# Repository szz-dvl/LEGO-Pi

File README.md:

LEGO-Pi
=======

This is my final degree project. Its is a HAL to control LEGO peripherals from a Raspberry Pi, for more detailed info please refer to the [docs](https://github.com/szz-dvl/LEGO-Pi/tree/master/docs) directory.

## Acknowledgments

* F.I.B: Facultad d'Informàtica de Barcelona.

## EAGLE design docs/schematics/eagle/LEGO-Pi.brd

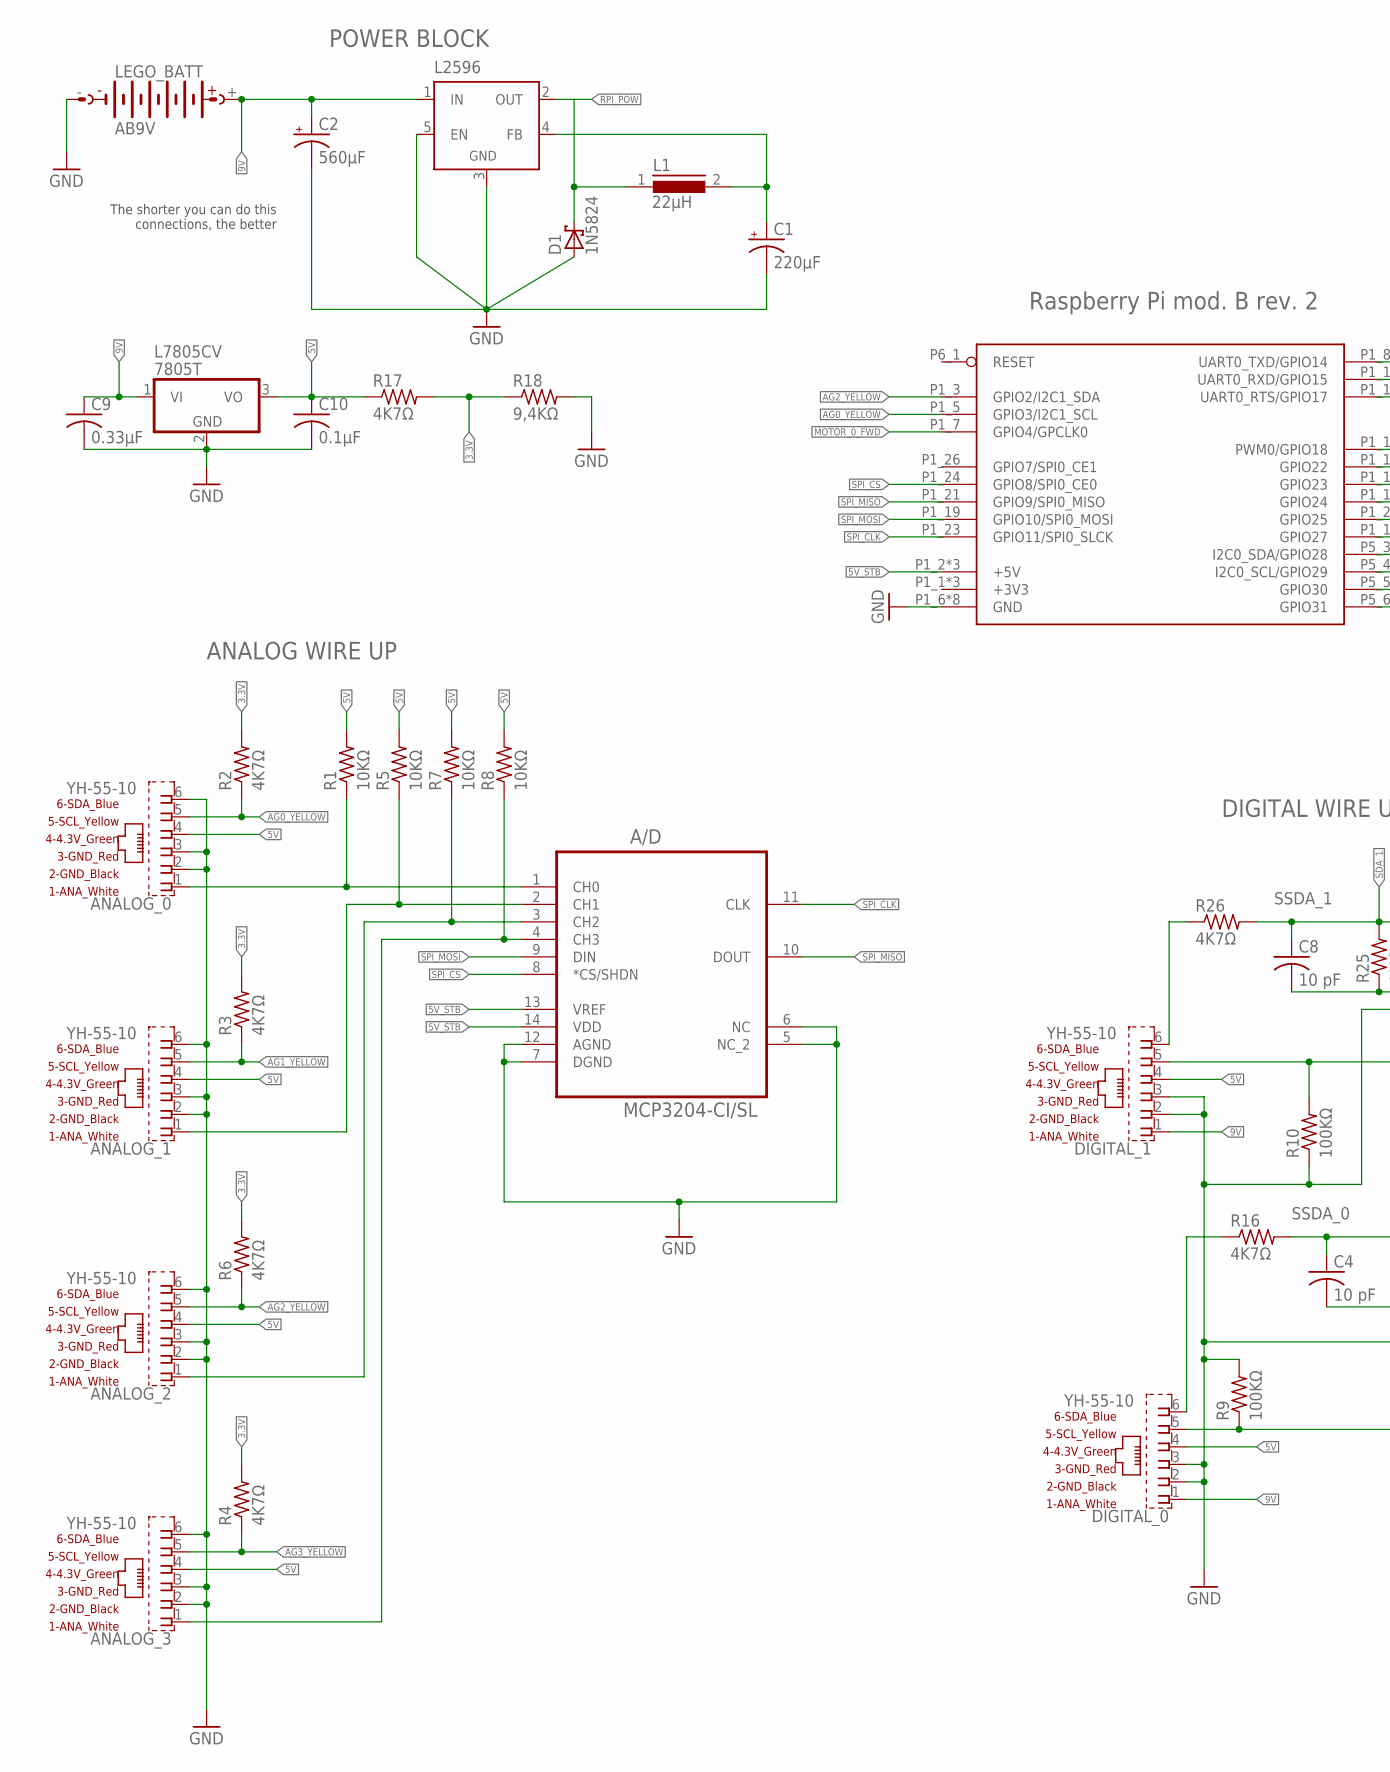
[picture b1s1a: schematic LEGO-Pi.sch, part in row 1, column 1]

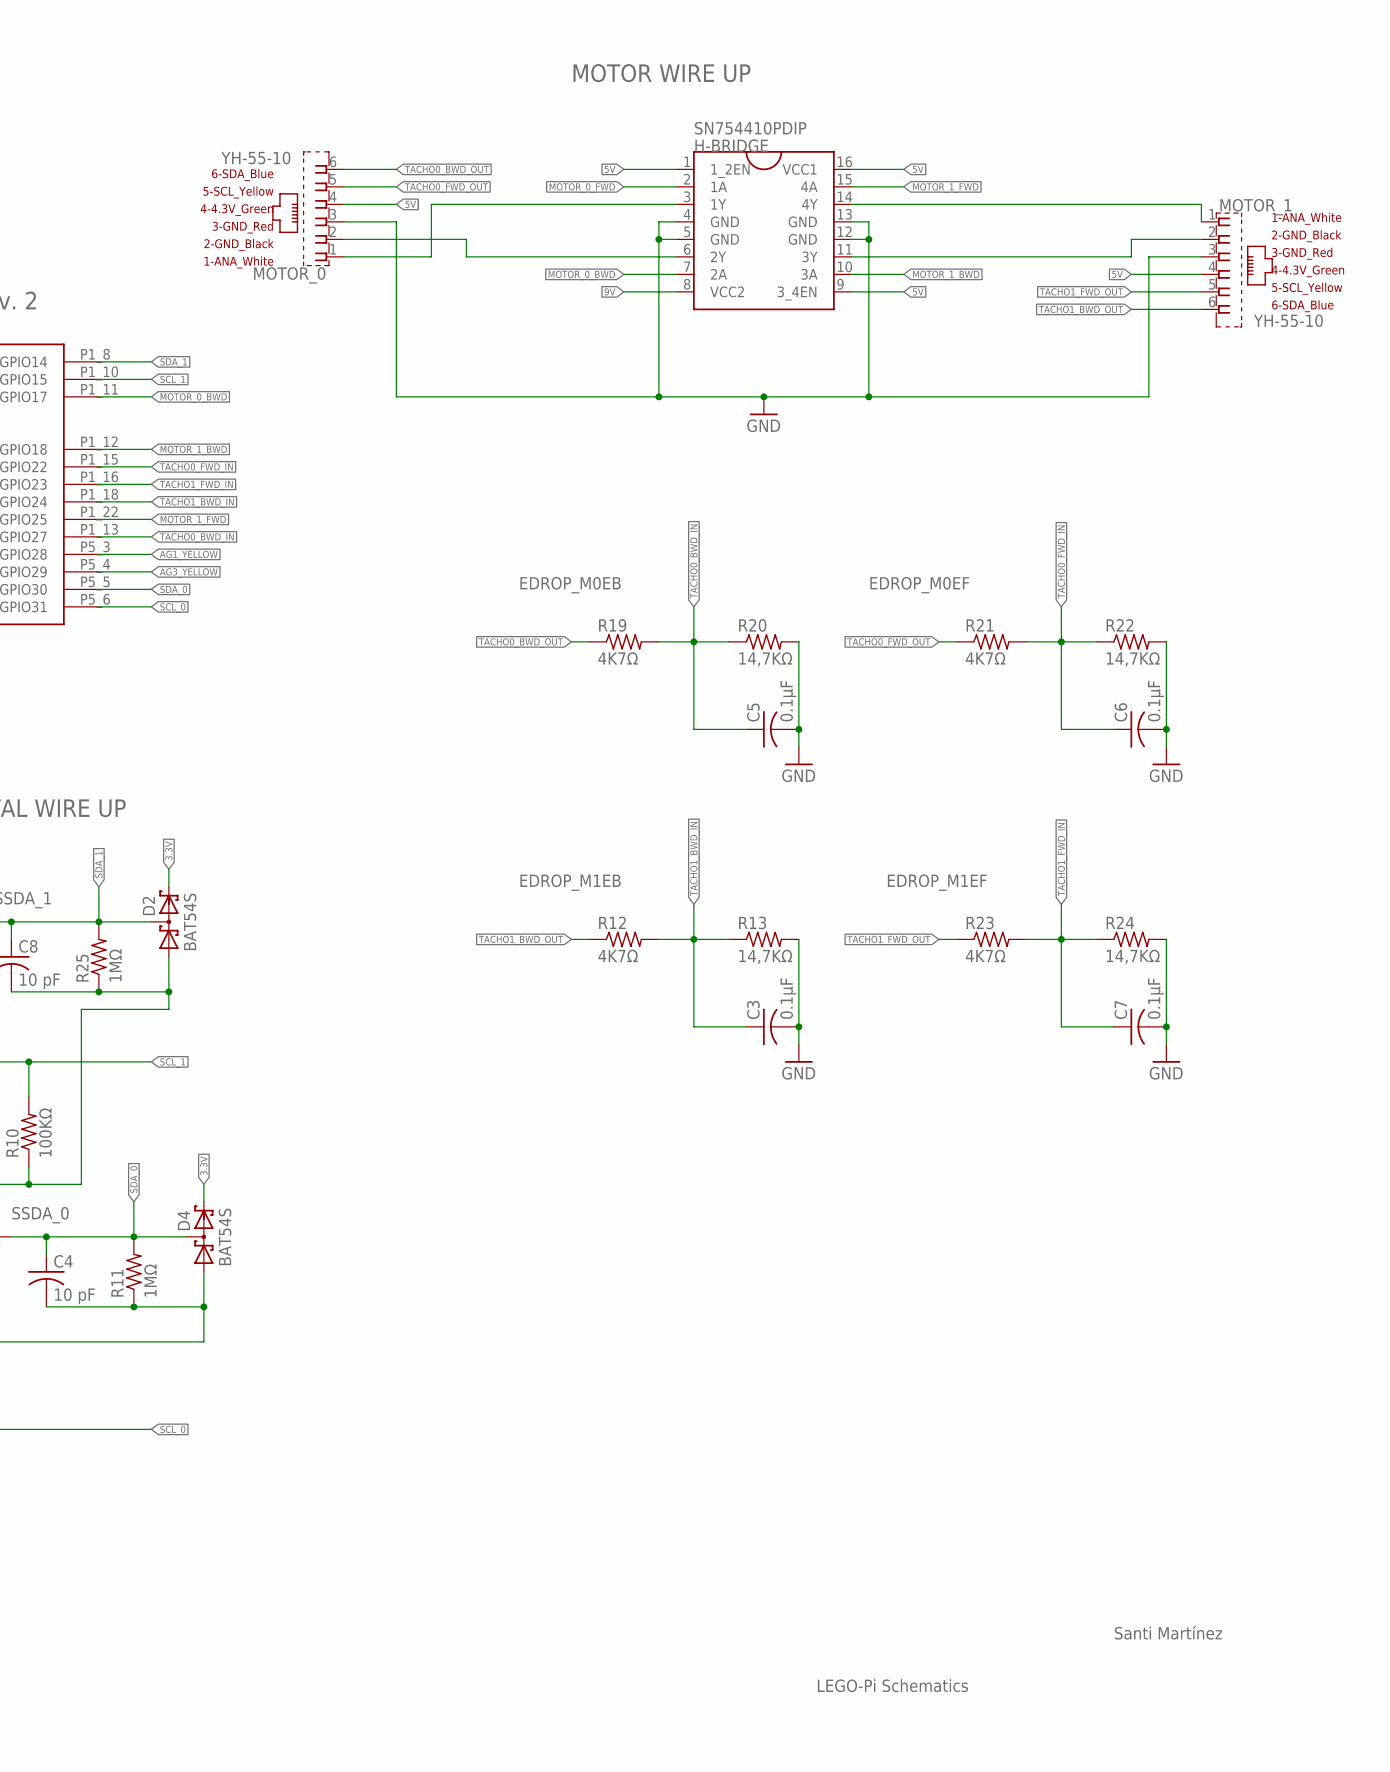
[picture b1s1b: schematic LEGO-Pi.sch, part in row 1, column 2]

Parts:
A/D: MCP3204-CI/SL; SOIC127P600X175-14N
ANALOG_0, ANALOG_1, ANALOG_2, ANALOG_3: YH-55-10
C1: 220µF; 085CS_1AR
C2: 560µF; 085CS_1AR
C3, C5, C6, C7, C10: 0.1µF; C025-024X044
C4, C8: 10 pF; C025-024X044
C9: 0.33µF; C025-024X044
D1: 1N5824; C4111-15
D2, D4: BAT54S; SOT23
DIGITAL_0, DIGITAL_1: YH-55-10
H-BRIDGE: SN754410PDIP; DIL16
L1: 22µH; SFT1040
L2596: LM2596TH; TO220-52
L7805CV: 7805T; TO220H
LEGO_BATT: AB9V
MOTOR_0, MOTOR_1: YH-55-10
R1, R5, R7, R8: 10KΩ; 0204V
R2, R3, R4, R6: 4K7Ω; 0204V
R9, R10: 100KΩ; 0204V
R11, R25: 1MΩ; 0207/5V
R12, R16, R17, R19, R21, R23, R26: 4K7Ω; 0207/5V
R13, R20, R22, R24: 14,7KΩ; 0207/5V
R18: 9,4KΩ; 0207/5V
U$1: RPI-B-V2; RPI-A-SHIELD

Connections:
3.3V: D2.2 (C2), D4.2 (C2), R2.2, R3.2, R4.2, R6.2, R17.2, R18.1
5V: ANALOG_0.4 (4_4.3V_GREEN), ANALOG_1.4 (4_4.3V_GREEN), ANALOG_2.4 (4_4.3V_GREEN), ANALOG_3.4 (4_4.3V_GREEN), C10.1, DIGITAL_0.4 (4_4.3V_GREEN), DIGITAL_1.4 (4_4.3V_GREEN), H-BRIDGE.1 (1_2EN), H-BRIDGE.9 (3_4EN), H-BRIDGE.16 (VCC1), L7805CV.3 (VO), MOTOR_0.4 (4_4.3V_GREEN), MOTOR_1.4 (4_4.3V_GREEN), R1.2, R5.2, R7.2, R8.2, R17.1
5V_STB: A/D.13 (VREF), A/D.14 (VDD), U$1.P1_2 (+5V), U$1.P1_4 (+5V), U$1.P5_1 (+5V)
9V: C2.+, C9.1, DIGITAL_0.1 (1_ANA_WHITE), DIGITAL_1.1 (1_ANA_WHITE), H-BRIDGE.8 (VCC2), L2596.1 (IN), L7805CV.1 (VI), LEGO_BATT.+
+3V3: U$1.P1_1 (+3V3), U$1.P1_17 (+3V3), U$1.P5_2 (+3V3)
AG0_YELLOW: ANALOG_0.5 (5_SCL_YELLOW), R2.1, U$1.P1_5 (GPIO3/I2C1_SCL)
AG1_YELLOW: ANALOG_1.5 (5_SCL_YELLOW), R3.1, U$1.P5_3 (I2C0_SDA/GPIO28)
AG2_YELLOW: ANALOG_2.5 (5_SCL_YELLOW), R6.1, U$1.P1_3 (GPIO2/I2C1_SDA)
AG3_YELLOW: ANALOG_3.5 (5_SCL_YELLOW), R4.1, U$1.P5_4 (I2C0_SCL/GPIO29)
GND: A/D.5 (NC_2), A/D.6 (NC), A/D.7 (DGND), A/D.12 (AGND), ANALOG_0.2 (2_GND_BLACK), ANALOG_0.3 (3_GND_RED), ANALOG_0.6 (6_SDA_BLUE), ANALOG_1.2 (2_GND_BLACK), ANALOG_1.3 (3_GND_RED), ANALOG_1.6 (6_SDA_BLUE), ANALOG_2.2 (2_GND_BLACK), ANALOG_2.3 (3_GND_RED), ANALOG_2.6 (6_SDA_BLUE), ANALOG_3.2 (2_GND_BLACK), ANALOG_3.3 (3_GND_RED), ANALOG_3.6 (6_SDA_BLUE), C1.-, C2.-, C3.2, C4.2, C5.2, C6.2, C7.2, C8.2, C9.2, C10.2, D1.A, D2.1 (A1), D4.1 (A1), DIGITAL_0.2 (2_GND_BLACK), DIGITAL_0.3 (3_GND_RED), DIGITAL_1.2 (2_GND_BLACK), DIGITAL_1.3 (3_GND_RED), H-BRIDGE.4 (GND), H-BRIDGE.5 (GND), H-BRIDGE.12 (GND), H-BRIDGE.13 (GND), L2596.3 (GND), L2596.5 (EN), L7805CV.2 (GND), LEGO_BATT.-, MOTOR_0.3 (3_GND_RED), MOTOR_1.3 (3_GND_RED), R9.2, R10.1, R11.1, R13.2, R18.2, R20.2, R22.2, R24.2, R25.1, U$1.P1_6 (GND), U$1.P1_9 (GND), U$1.P1_14 (GND), U$1.P1_20 (GND), U$1.P1_25 (GND), U$1.P5_7 (GND), U$1.P5_8 (GND), U$1.P6_2 (GND)
MOTOR_0_BWD: H-BRIDGE.7 (2A), U$1.P1_11 (UART0_RTS/GPIO17)
MOTOR_0_FWD: H-BRIDGE.2 (1A), U$1.P1_7 (GPIO4/GPCLK0)
MOTOR_1_BWD: H-BRIDGE.10 (3A), U$1.P1_12 (PWM0/GPIO18)
MOTOR_1_FWD: H-BRIDGE.15 (4A), U$1.P1_22 (GPIO25)
unnamed: H-BRIDGE.14 (4Y), MOTOR_1.1 (1_ANA_WHITE)
unnamed: H-BRIDGE.11 (3Y), MOTOR_1.2 (2_GND_BLACK)
unnamed: A/D.2 (CH1), ANALOG_1.1 (1_ANA_WHITE), R5.1
unnamed: A/D.1 (CH0), ANALOG_0.1 (1_ANA_WHITE), R1.1
unnamed: C1.+, L1.2, L2596.4 (FB)
unnamed: A/D.3 (CH2), ANALOG_2.1 (1_ANA_WHITE), R7.1
unnamed: A/D.4 (CH3), ANALOG_3.1 (1_ANA_WHITE), R8.1
unnamed: H-BRIDGE.6 (2Y), MOTOR_0.2 (2_GND_BLACK)
unnamed: H-BRIDGE.3 (1Y), MOTOR_0.1 (1_ANA_WHITE)
unnamed: DIGITAL_0.6 (6_SDA_BLUE), R16.1
unnamed: DIGITAL_1.6 (6_SDA_BLUE), R26.1
RESET: U$1.P6_1 (RESET)
RPI_POW: D1.C, L1.1, L2596.2 (OUT)
SCL_0: DIGITAL_0.5 (5_SCL_YELLOW), R9.1, U$1.P5_6 (GPIO31)
SCL_1: DIGITAL_1.5 (5_SCL_YELLOW), R10.2, U$1.P1_10 (UART0_RXD/GPIO15)
SDA_0: C4.1, D4.3 (C1A2), R11.2, R16.2, U$1.P5_5 (GPIO30)
SDA_1: C8.1, D2.3 (C1A2), R25.2, R26.2, U$1.P1_8 (UART0_TXD/GPIO14)
SPI_CLK: A/D.11 (CLK), U$1.P1_23 (GPIO11/SPI0_SLCK)
SPI_CS: A/D.8 (*CS/SHDN), U$1.P1_24 (GPIO8/SPI0_CE0)
SPI_MISO: A/D.10 (DOUT), U$1.P1_21 (GPIO9/SPI0_MISO)
SPI_MOSI: A/D.9 (DIN), U$1.P1_19 (GPIO10/SPI0_MOSI)
TACHO0_BWD_IN: C5.1, R19.2, R20.1, U$1.P1_13 (GPIO27)
TACHO0_BWD_OUT: MOTOR_0.6 (6_SDA_BLUE)
TACHO0_FWD_IN: C6.1, R21.2, R22.1, U$1.P1_15 (GPIO22)
TACHO0_FWD_OUT: MOTOR_0.5 (5_SCL_YELLOW)
TACHO1_BWD_IN: C3.1, R12.2, R13.1, U$1.P1_18 (GPIO24)
TACHO1_BWD_OUT: MOTOR_1.6 (6_SDA_BLUE), R12.1
TACHO1_FWD_IN: C7.1, R23.2, R24.1, U$1.P1_16 (GPIO23)
TACHO1_FWD_OUT: MOTOR_1.5 (5_SCL_YELLOW), R23.1

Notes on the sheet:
Santi Martínez
LEGO-Pi Schematics
POWER BLOCK
Raspberry Pi mod. B rev. 2
MOTOR WIRE UP
The shorter you can do this connections, the better
ANALOG WIRE UP
SSDA_0
SSDA_1
DIGITAL WIRE UP
EDROP_M0EB
EDROP_M0EF
EDROP_M1EF
EDROP_M1EB

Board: 2 copper layers, 52 parts (0 on the bottom side), 40 nets, no tracks yet.

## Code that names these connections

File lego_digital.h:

/*
* This file is part of LEGO-Pi.
*
* Copyright (Copyplease) szz-dvl.
*
*
* License
*
* This program is free software: you can redistribute it and/or modify
* it under the terms of the GNU Affero General Public License as published
* by the Free Software Foundation, either version 3 of the License, or
* (at your option) any later version.
*
* This program is distributed in the hope that it will be useful,
* but WITHOUT ANY WARRANTY; without even the implied warranty of
* MERCHANTABILITY or FITNESS FOR A PARTICULAR PURPOSE. See the
* GNU Affero General Public License for more details at
* <http://www.gnu.org/licenses/agpl-3.0-standalone.html>
*/

#include "lego_shared.h"
#include <lego/lego_i2c.h>

#define LEGO_ADDR        0x02 
#define LEGO_FREQ        9600 //baudios/Hz
#define SDA_0            30
#define SCL_0            31
#define SDA_1            14
#define SCL_1            15

#define CMD_REG          0x41
#define MAX_PORT_DG      1
#define MIN_PORT_DG      0

#define RAW_LEN          2
#define US_DWAIT         4000
#define US_IWAIT         3000
#define US_CWAIT         19000 
#define HT_DLY           0
#define DEF_DELAY        5000

#define IN_MAX_LEN       8
#define MAX_IRS_STR      5 
#define MAX_US_DIST      7 

#define US_INF_MAX_OFFS  8 
#define HT_INF_MAX_OFFS  3

#define US_CMD_RMIN      0
#define US_CMD_RMAX      4

#define HTCS_CMD_RMIN    5
#define HTCS_CMD_RMAX    10

#define HTCM_CMD_RMIN    11
#define HTCM_CMD_RMAX    12

#define HTIS_CMD_RMIN    13
#define HTIS_CMD_RMAX    14

#define IS_US_CMD(c)     (c >= US_CMD_RMIN && c <= US_CMD_RMAX)
#define IS_HTCS_CMD(c)   (c >= HTCS_CMD_RMIN && c <= HTCS_CMD_RMAX)
#define IS_HTCM_CMD(c)   (c >= HTCM_CMD_RMIN && c <= HTCM_CMD_RMAX)
#define IS_HTIS_CMD(c)   (c >= HTIS_CMD_RMIN && c <= HTIS_CMD_RMAX)

#define IS_HITECH(x)     (x>1)

//Meant to be used by the developer
#define US_DIST_TABLE_TAM 8
#define IRS_STR_TABLE_TAM 5  
#define DG_INFO_TABLE_TAM 9

typedef enum {
  
  DG_OTHER,
  LEGO_US,
  HT_COMPASS,
  HT_ACCEL,
  HT_COLOR,
  HT_IRS

} dgType;

struct digital_device {
  
  dgType type;
  int port;
  int vers;
  I2C_DVC * dvc;

};
typedef struct digital_device DGDVC;

struct sensor_command {

  uint8_t reg;
  uint8_t val;
  int delay;
  int minvrs;

};
typedef struct sensor_command CMD;

struct sensor_msg {
  
  uint8_t base;
  int len;
  int delay;
  int minvrs; 

};
typedef struct sensor_msg MSG;

typedef enum {

  US_OFF,
  US_SIN_SHOT,
  US_CONT_MES,
  US_EVENT_CAP,
  US_WARM_RESET,
  HTCS_CAL_WHITE,
  HTCS_ACT_MD,
  HTCS_PAS_MD,
  HTCS_RAW_MD,
  HTCS_50_MD,
  HTCS_60_MD,
  HTCM_MES_MD,
  HTCM_CAL_MD,
  HTIS_DSP_12,
  HTIS_DSP_6,

} cmdIdx;

typedef enum {

  HT_VER_NUM,
  HT_MANFAC,
  HT_SEN_TYPE,
  HT_STATE,
  HTCS_COL_NUM,
  HTCS_RED,
  HTCS_GREEN,
  HTCS_BLUE,
  HTCS_RAW_RED,
  HTCS_RAW_GREEN,
  HTCS_RAW_BLUE,
  HTCS_COL_IDX,
  HTCS_NRM_RED,
  HTCS_NRM_GREEN,
  HTCS_NRM_BLUE,
  HTCS2_WHITE,
  HTCS2_COL_IDX,
  HTCS2_NRM_RED,
  HTCS2_NRM_GREEN,
  HTCS2_NRM_BLUE,
  HTCS2_RAW_RED,
  HTCS2_RAW_GREEN,
  HTCS2_RAW_BLUE,
  HTCS2_RAW_WHITE,
  HTIS_DC_DIR,
  HTIS_DCSTR_1,
  HTIS_DCSTR_2,
  HTIS_DCSTR_3,
  HTIS_DCSTR_4,
  HTIS_DCSTR_5,
  HTIS_DC_AVG,
  HTIS_AC_DIR,
  HTIS_ACSTR_1,
  HTIS_ACSTR_2,
  HTIS_ACSTR_3,
  HTIS_ACSTR_4,
  HTIS_ACSTR_5,
  HTAC_X_UP,
  HTAC_Y_UP,
  HTAC_Z_UP,
  HTAC_X_LW,
  HTAC_Y_LW,
  HTAC_Z_LW,
  HTCM_2_DEG,
  HTCM_1_ADD,
  HTCM_HEAD,
  US_PR_VER,
  US_PR_ID,
  US_SEN_TYPE,
  US_FAC_ZERO,
  US_FAC_SC_FAC,
  US_FAC_SC_DIV,
  US_MES_UNITS,
  US_MES_INT,
  US_STATE,
  US_DIST_0,
  US_DIST_1,
  US_DIST_2,
  US_DIST_3,
  US_DIST_4,
  US_DIST_5,
  US_DIST_6,
  US_DIST_7

}msgIdx;

/*This ones allways return 0xFF to me, I think the registers aren't available, however may be more recent versions if the Ultrasonic supporting it....*/
//{0x50, 1, IWAIT, "Actual Zero: "}, 
//{0x51, 1, IWAIT, "Actual Scale Factor: "},
//{0x52, 1, IWAIT, "Actual Scale Divisor: "},

extern bool dg_init(int retry);
extern bool dg_set_verbose(int lvl);
extern bool dg_new (DGDVC * dev, dgType type, int port);
extern bool dg_new_unknown (DGDVC * dev, uint8_t addr, int freq, int port);
extern void dg_shutdown ();
extern bool dg_send_cmd (DGDVC * dev, cmdIdx cmd);
extern bool dg_get_state (DGDVC * dvc, uint8_t * state);
extern bool dg_col_get_rgb (DGDVC * dvc, uint8_t * red, uint8_t * green, uint8_t * blue);
extern bool dg_col_get_norm (DGDVC * dvc, uint8_t * red, uint8_t * green, uint8_t * blue);
extern bool dg_col_get_index (DGDVC * dvc, uint8_t * idx);
extern bool dg_col_get_number (DGDVC * dvc, uint8_t * num);
extern bool dg_col_get_white (DGDVC * dvc, uint16_t * white, bool raw, bool passive);
extern bool dg_col_get_raw (DGDVC * dvc, uint16_t * red, uint16_t * green, uint16_t * blue, bool passive);
extern bool dg_irs_get_dir (DGDVC * dvc, uint8_t * dir, bool dc);
extern bool dg_irs_get_str (DGDVC * dvc, uint8_t * str, int num, bool dc);
extern bool dg_irs_get_dcavg (DGDVC * dvc, uint8_t * avg);
extern bool dg_irs_get_allstr (DGDVC * dvc, uint8_t * strt, bool dc);
extern bool dg_us_get_dist (DGDVC * dvc, uint8_t * dist, int num);
extern bool dg_us_get_alldist (DGDVC * dvc, uint8_t tdist []);
extern bool dg_com_get_head (DGDVC * dvc, uint16_t * h1, uint16_t * h2);
extern bool dg_acc_get_axis (DGDVC * dvc, int * x, int * y, int * z);
extern bool dg_get_info (DGDVC * dvc, char * info [], bool titled);
extern bool dg_transfer (DGDVC * dev, uint8_t data_out [], int len_out, bool rs, uint16_t data_in [], int len_in, bool word_read, int cse);
extern bool dg_write (DGDVC * dev, uint8_t data_out [], int len_out, int cse);
extern bool dg_read (DGDVC * dev, uint16_t data_in [], int len_in, bool word_read, int cse);

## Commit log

2014-03-01 this is the first dirty version of my project
2014-03-14 revised
2014-04-21 added digital support
2014-04-21 anybody knows how to make externals not modifiabl??
2014-04-21 tyding up
2014-04-22 fixing motor externals
2014-04-22 fixing dirs
2014-04-22 fixing motors
2014-04-22 stage 1
2014-04-24 motors stage 2
2014-04-24 tyding up analogs
2014-04-25 integration stage 1
2014-04-25 digitals ALMOST ready...
2014-04-26 yellow wire hardware redesigned
2014-04-26 added sound sensor support
2014-04-26 added ht_gyro sensor support
2014-04-26 analog minor tyding
2014-04-27 digital hardware interface testing
2014-05-01 cleaning up motors
2014-05-01 some kind of motors "final version"
2014-05-07 dreadlock
2014-05-07 DO NOT TRUST THE WEB
2014-05-12 ending motors
2014-05-12 first robot assembly
2014-05-12 more motors
2014-05-12 la cosa nostra...
2014-05-12 don't mess with WiringPi
2014-05-12 more&&more&&more&&...
2014-05-27 bad bad bad news \dots
2014-06-01 fixing analogs
2014-06-02 analog working as expected
2014-06-03 taking shape
2014-06-03 really finishing motors
2014-06-03 motor encoder interrupts working fine
2014-06-03 tidying up
2014-06-04 added yellow wire control for unknown analog dvcs
2014-06-04 main file rearrangement
2014-06-04 fixing tests
2014-06-05 test stage 2
2014-06-05 tests done but optarg
2014-06-05 ending tests
2014-06-06 more on tests
2014-06-06 shit
2014-06-06 tests clean
2014-06-06 MIN_VEL fixed
2014-06-07 test push
2014-06-08 added support for both motors at a time 3 & 4
2014-06-08 added two motors at a time support for 5
2014-06-09 minor fixing
2014-06-09 difft as a macro
2014-06-09 mt_wait_all little mod
2014-06-09 tests more flexible
2014-06-11 test fix
2014-06-12 fixing tests.
2014-06-12 syncro issue
2014-06-12 analog fixing
2014-06-13 digital fixings
2014-06-15 motor tticks fix
2014-06-15 ag_gyro_cal fixing
2014-06-15 "fixed" calibration for HT_COMPASS
2014-06-15 documentation
2014-06-16 without patch
2014-06-16 repatched
2014-06-16 install script
2014-06-16 inst script
2014-06-16 dynamic patch creation.
2014-06-16 dynamic patch creation
2014-06-18 memoir rearrangement
2014-06-18 licenceç
2014-06-18 add local wpi
2014-06-18 new wpi
2014-06-18 last wpi
2014-06-18 renew
2014-06-18 first ver
2014-06-18 missing options yet...
2014-06-18 fixings
2014-06-18 memoir
2014-06-23 sincro first
2014-06-23 demo
2014-06-24 delay_us supporting +1sec
2014-06-30 demo last
2014-07-07 added Arch-Linux support [-f]
2018-08-14 README

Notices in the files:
parts and their libraries:
raspberry: This library stands under the CERN Open Hardware Licence.
